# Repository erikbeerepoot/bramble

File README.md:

# Bramble

LoRa sensor and actuator network for farm monitoring, built on RP2040.

Hub-and-spoke architecture: a central hub manages the network while nodes collect sensor data (temperature, humidity) and control actuators (irrigation valves). LoRa provides long-range wireless with reliable delivery guarantees.

## Hardware

- Adafruit Feather RP2040 LoRa (SX1276, 915 MHz)
- MT25QL01GBBB 128MB external flash for sensor data storage
- STM32L010 PMU for power management and sleep

## Building

Requires the Pico SDK. CMake is bundled at `~/.pico-sdk/cmake/v3.31.5/bin/cmake`.

```bash
# Build a specific variant
cmake -B build -DHARDWARE_VARIANT=SENSOR
cmake --build build -j8

# Variants: SENSOR, IRRIGATION, CONTROLLER, HUB, GENERIC, ALL
```

Each variant produces a named executable (e.g. `bramble_sensor.uf2`).

```bash
# Run tests
cmake -B build -DBUILD_TESTS=ON
cmake --build build -j8
```

### Flashing

Hold BOOTSEL and connect via USB, then copy the `.uf2` file. Or use OpenOCD with a debug probe:

```bash
~/.pico-sdk/openocd/0.12.0+dev/openocd \
  -s ~/.pico-sdk/openocd/0.12.0+dev/scripts \
  -f interface/cmsis-dap.cfg -f target/rp2040.cfg \
  -c "adapter speed 5000" \
  -c "program build/bramble_sensor.elf verify reset exit"
```

## Architecture

```
[Sensor Nodes] --LoRa--> [Hub/Pico] --Serial--> [Raspberry Pi] --REST--> [Dashboard]
                               |                       |
                          128MB Flash              DuckDB
                        (local buffer)          (long-term storage)
```

### Firmware (`src/`)

- `modes/` - Application modes per hardware variant (sensor, irrigation, hub, etc.)
- `lora/` - SX1276 driver, message protocol, reliable delivery, routing
- `hal/` - Hardware abstraction (flash, NeoPixel, valves, SPI)
- `storage/` - 128MB circular flash buffer for sensor records
- `config/` - Persistent node/hub configuration

### API (`api/`)

Flask REST API on the Raspberry Pi. Receives sensor data from the hub over serial, stores in DuckDB.

```bash
cd api && uv sync && uv run app.py
```

### Dashboard (`dashboard/`)

React SPA for viewing sensor data, managing nodes, and organizing zones.

```bash
cd dashboard && npm install && npm run dev
```

## Setup

After cloning:

```bash
./setup.sh  # configures git hooks
```

See `CLAUDE.md` for development guidelines and `PLAN.md` for the roadmap.

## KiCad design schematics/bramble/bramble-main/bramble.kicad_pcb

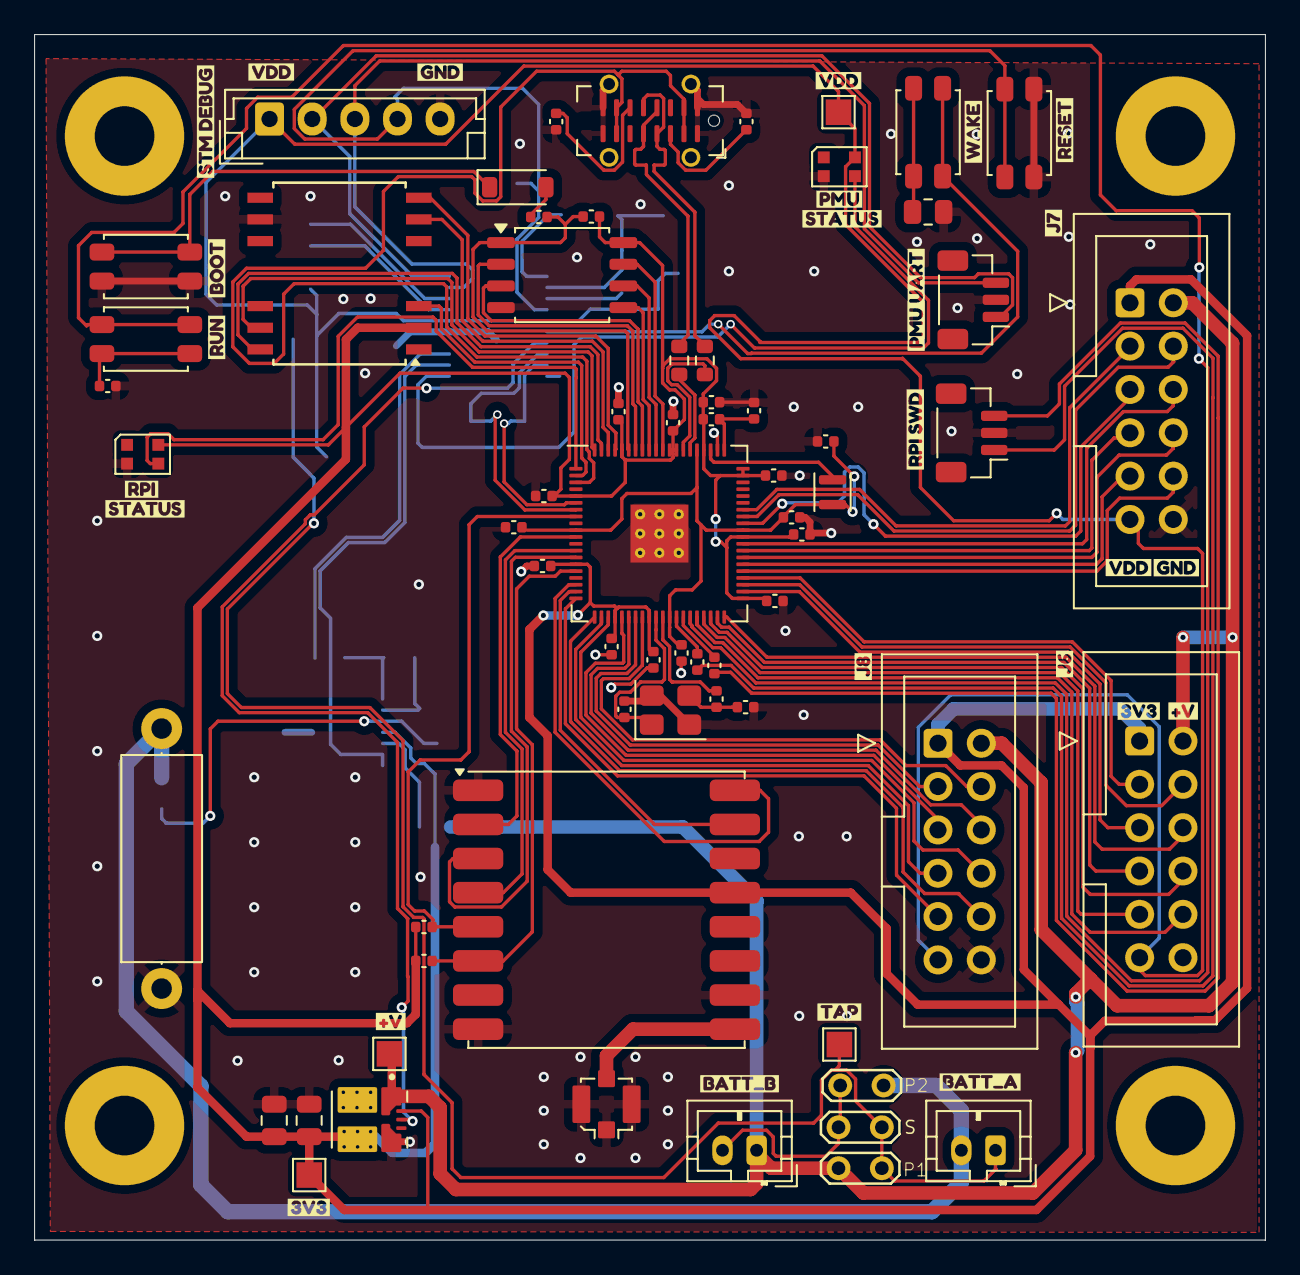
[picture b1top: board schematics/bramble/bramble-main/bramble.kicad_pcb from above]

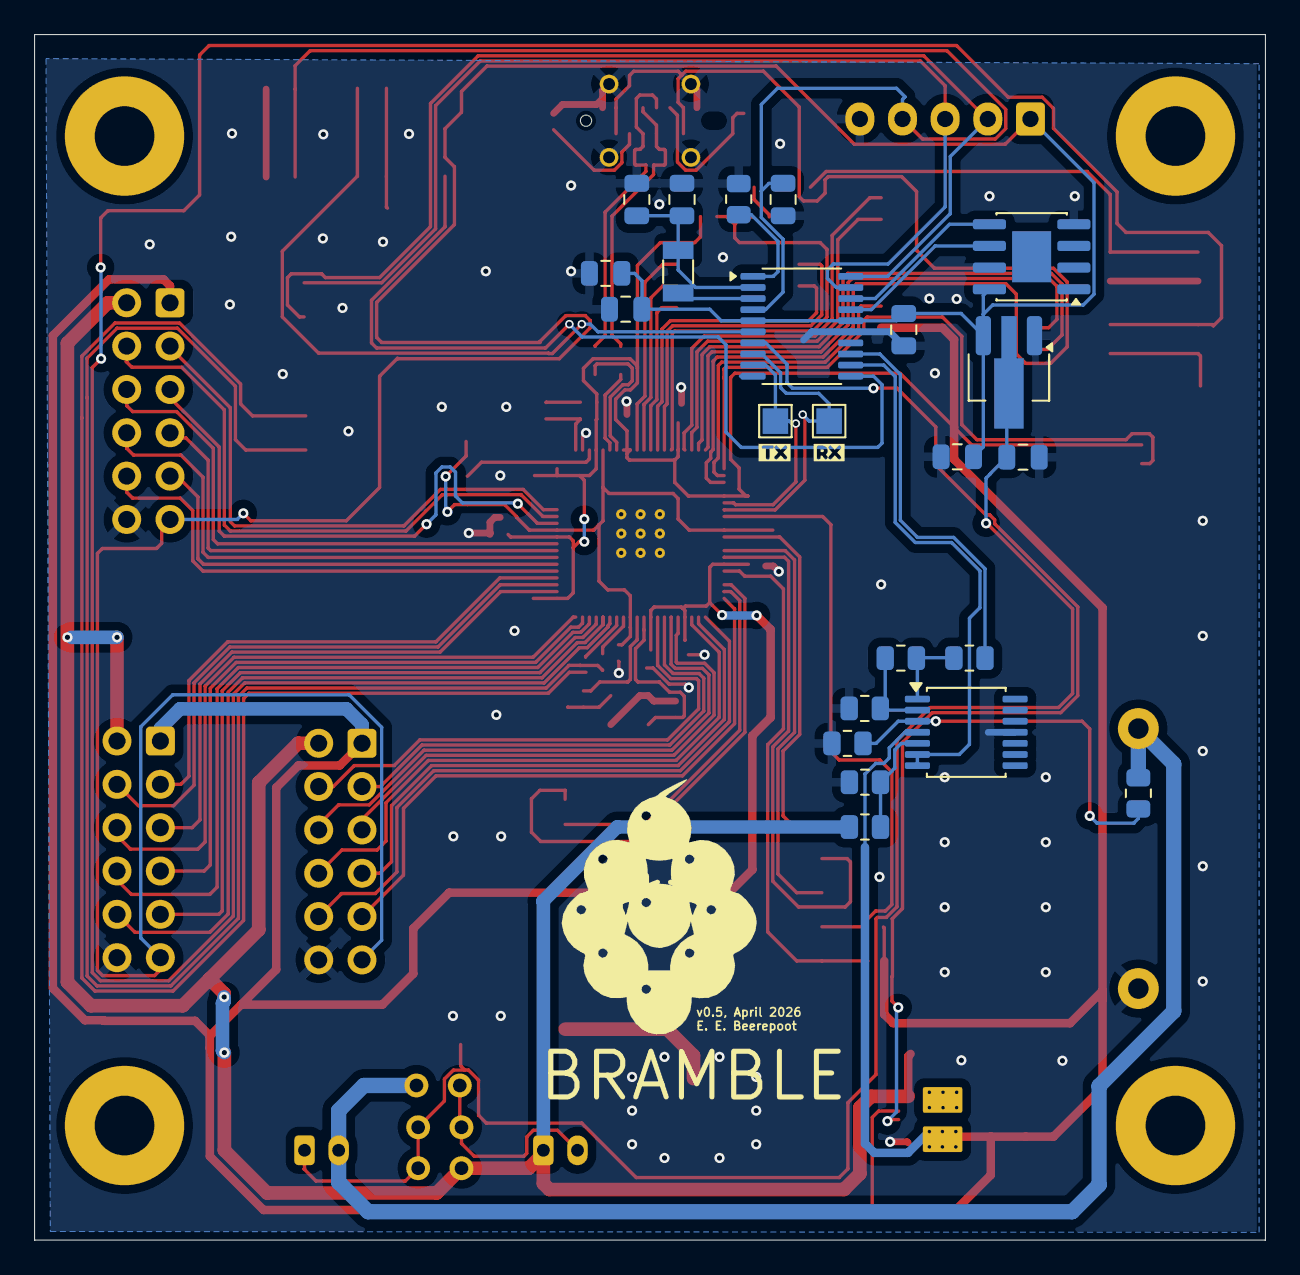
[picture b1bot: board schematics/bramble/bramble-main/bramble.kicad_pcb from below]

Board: 2 copper layers, 72.1 x 70.7 mm, 120 parts (25 on the bottom side), 91 nets.

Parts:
C1: 10uF; C_0805_2012Metric
C2: 22uF; C_0805_2012Metric
C3: 4.7uF; C_0805_2012Metric
C4, C5, C8: 100nF; C_0805_2012Metric
C6, C7: 1uF; C_0805_2012Metric
C9, C10: 10pF; C_0805_2012Metric
C11, C12, C14, C15: 4.7uF; C_0402_1005Metric
C13, C16, C17, C18, C19, C20, C21, C22, C23, C24, C27: 100nF; C_0402_1005Metric
C25, C26: 15p; C_0402_1005Metric
D1: 1N4148W; D_SOD-123
H1, H2, H3, H4: MountingHole; MountingHole_3.5mm_Pad
J1: Conn_01x05_Pin; JST_EH_B5B-EH-A_1x05_P2.50mm_Vertical
J2: UART; JST_SH_BM03B-SRSS-TB_1x03-1MP_P1.00mm_Vertical
J3: RPI SWD; JST_SH_BM03B-SRSS-TB_1x03-1MP_P1.00mm_Vertical
J4: U.FL; U.FL_Molex_MCRF_73412-0110_Vertical
J5: USB_C_Receptacle_USB2.0_16P; USB_C_Receptacle_G-Switch_GT-USB-7051x
J6: GPIO1; IDC-Header_2x06_P2.54mm_Vertical
J7: GPIO2; IDC-Header_2x06_P2.54mm_Vertical
J8: GPIO3; IDC-Header_2x06_P2.54mm_Vertical
JP1: Series; TestPoint_2Pads_Pitch2.54mm_Drill0.8mm
JP2: Parallel 1; TestPoint_2Pads_Pitch2.54mm_Drill0.8mm
JP3: Parallel 2; TestPoint_2Pads_Pitch2.54mm_Drill0.8mm
L1: 3.3uH; L_Murata_DFE201610P
MAIN_SUPPLY1: B2B-PH-K-S; JST_PH_B2B-PH-K_1x02_P2.00mm_Vertical
PMU_STATUS1: WS2812B-2020; LED_WS2812B-2020_PLCC4_2.0x2.0mm
PMU_SUPPLY1: B2B-PH-K-S; JST_PH_B2B-PH-K_1x02_P2.00mm_Vertical
R1, R3, R6: 1k; R_0805_2012Metric
R2: 100; R_0805_2012Metric
R4: 0.1; R_Axial_DIN0414_L11.9mm_D4.5mm_P15.24mm_Horizontal
R5, R9, R10: 10k; R_0805_2012Metric
R7: 20k; R_0805_2012Metric
R8: 8.2k; R_0805_2012Metric
R11, R12, R23: 10k; C_0402_1005Metric
R13: 33; C_0402_1005Metric
R14, R15: 100; C_0402_1005Metric
R16, R17, R21, R22: 1K; C_0402_1005Metric
R18, R19: 27; R_0603_1608Metric
R20: 5.1K; C_0402_1005Metric
RPI_STATUS1: WS2812B-2020; LED_WS2812B-2020_PLCC4_2.0x2.0mm
STM_RESET1: STM_RESET; SW_SPST_EVQP2_MiddlePushTravel_H2.5mm
STM_WAKE1: STM_WAKE; SW_SPST_EVQP2_MiddlePushTravel_H2.5mm
SW1: BOOT; SW_SPST_EVQP2_MiddlePushTravel_H2.5mm
SW2: RESET; SW_SPST_EVQP2_MiddlePushTravel_H2.5mm
TP1: 3V3 TEST; TestPoint_Pad_1.5x1.5mm
TP2: RX_TEST; TestPoint_Pad_1.5x1.5mm
TP3: TX_TEST; TestPoint_Pad_1.5x1.5mm
TP4: MAINS TEST; TestPoint_Pad_1.5x1.5mm
TP5: TAP TEST; TestPoint_Pad_1.5x1.5mm
TP6: PMU SUPPLY TEST; TestPoint_Pad_1.5x1.5mm
U1: Opamp_Quad; TSSOP-14_4.4x5mm_P0.65mm
U2: STM32L031F6P6TR; TSSOP-20_4.4x6.5mm_P0.65mm
U3: MCP1700x-120xxMB; SOT-89-3_Handsoldering
U4: FM24CL16B-GTR; SOIC-8-1EP_3.9x4.9mm_P1.27mm_EP2.29x3mm
U5: NiceRF Lora1262; HOPERF_RFM9XW_SMD
U6: RP2350_80QFN; RP2350-QFN-80-1EP_10x10_P0.4mm_EP3.4x3.4mm_ThermalVias
U7: W25Q16JVSS; SOIC-8_5.3x5.3mm_P1.27mm
U8: MT25QL01GBBB8ESF-0SIT; SOIC-16W-12_7.5x10.3mm_P1.27mm
VR1: TPSM861253RDXR; VREG_TPSM861253RDXR
Y1: Crystal; Crystal_SMD_3215-2Pin_3.2x1.5mm
Y2: ABM8-272-T3; Crystal_SMD_3225-4Pin_3.2x2.5mm
kibuzzard-69F1F93E: G***; kibuzzard-69F1F93E
kibuzzard-69F1F948: G***; kibuzzard-69F1F948
kibuzzard-69F1FA9E: G***; kibuzzard-69F1FA9E
kibuzzard-69F1FABA: G***; kibuzzard-69F1FABA
kibuzzard-69F1FACD, kibuzzard-69F1FACD#2: G***; kibuzzard-69F1FACD
kibuzzard-69F1FAE9: G***; kibuzzard-69F1FAE9
kibuzzard-69F1FB2A, kibuzzard-69F1FB2A#2: G***; kibuzzard-69F1FB2A
kibuzzard-69F1FB3C: G***; kibuzzard-69F1FB3C
kibuzzard-69F1FB5C: G***; kibuzzard-69F1FB5C
kibuzzard-69F1FB6D: G***; kibuzzard-69F1FB6D
kibuzzard-69F1FB08: G***; kibuzzard-69F1FB08
kibuzzard-69F1FB43: G***; kibuzzard-69F1FB43
kibuzzard-69F1FBEC: G***; kibuzzard-69F1FBEC
kibuzzard-69F1FC5E: G***; kibuzzard-69F1FC5E
kibuzzard-69F15CED: G***; kibuzzard-69F15CED
kibuzzard-69F15D5F, kibuzzard-69F15D5F#2: G***; kibuzzard-69F15D5F
kibuzzard-69F15D28: G***; kibuzzard-69F15D28
kibuzzard-69F15D48, kibuzzard-69F15D48#2: G***; kibuzzard-69F15D48
kibuzzard-69F15DA2: G***; kibuzzard-69F15DA2
kibuzzard-69F20A0D: G***; kibuzzard-69F20A0D
kibuzzard-69F20A1A: G***; kibuzzard-69F20A1A
kibuzzard-69F204CF: G***; kibuzzard-69F204CF
kibuzzard-69F204DC: G***; kibuzzard-69F204DC
kibuzzard-69F209F9: G***; kibuzzard-69F209F9

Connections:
+1V1: C12.1, C13.1, C15.1, C16.1, L1.1, U6.10 (DVDD), U6.32 (DVDD), U6.51 (DVDD), U6.65 (VREG_FB)
+3V3: C1.1, C2.1, C11.1, C17.1, C18.1, C19.1, C20.1, C21.1, C22.1, C23.1, C24.1, C27.1, J6.1, J7.1, J8.1, R11.2, R12.2, R13.1, R23.1, RPI_STATUS1.4 (VDD), TP1.1, U1.4 (V+), U5.13 (3.3V), U6.5 (IOVDD), U6.15 (IOVDD), U6.24 (IOVDD), U6.29 (IOVDD), U6.41 (IOVDD), U6.50 (IOVDD), U6.59 (ADC_AVDD), U6.60 (IOVDD), U6.64 (VREG_VIN), U6.68 (USB_OTP_VDD), U6.69 (QSPI_IOVDD), U6.76 (IOVDD), U7.8 (VCC), U8.2 (VCC), VR1.3 (VOUT), VR1.7 (VOS)
+9V: J6.2, J7.2, J8.2, JP2.1 (A), MAIN_SUPPLY1.1, R7.2, TP4.1, VR1.1 (VIN)
/pmu/3V3_POWER_ON: U2.7 (PA1), VR1.6 (EN)
/pmu/MEAS_CURRENT: R6.1, U2.13 (PA7)
/pmu/MEAS_V: U1.6 (-), U1.7, U2.12 (PA6)
/pmu/NRST: C8.2, J1.4, STM_RESET1.1, U2.4 (NRST)
/pmu/SCL: U2.17 (PA9), U4.6 (SCL)
/pmu/SDA: U2.18 (PA10), U4.5 (SDA)
/rp2350B (page 4)/D+: J5.A6 (D+), J5.B6 (D+), R18.2
/rp2350B (page 4)/D-: J5.A7 (D-), J5.B7 (D-), R19.2
/rp2350B (page 4)/GPIO20: J8.9, U6.20 (GPIO20)
/rp2350B (page 4)/GPIO21: J8.10, U6.21 (GPIO21)
/rp2350B (page 4)/GPIO22: J8.7, U6.22 (GPIO22)
/rp2350B (page 4)/GPIO23: J8.8, U6.23 (GPIO23)
/rp2350B (page 4)/GPIO24: J8.5, U6.25 (GPIO24)
/rp2350B (page 4)/GPIO25: J8.6, U6.26 (GPIO25)
/rp2350B (page 4)/GPIO26: J8.3, U6.27 (GPIO26)
/rp2350B (page 4)/GPIO27: J8.4, U6.28 (GPIO27)
/rp2350B (page 4)/GPIO28: J7.10, U6.45 (GPIO36)
/rp2350B (page 4)/GPIO29: J7.9, U6.46 (GPIO37)
/rp2350B (page 4)/GPIO30: J7.8, U6.47 (GPIO38)
/rp2350B (page 4)/GPIO31: J7.7, U6.48 (GPIO39)
/rp2350B (page 4)/GPIO40_ADC0: J7.6, U6.49 (GPIO40_ADC0)
/rp2350B (page 4)/GPIO41_ADC1: J7.5, U6.52 (GPIO41_ADC1)
/rp2350B (page 4)/GPIO42_ADC2: J7.4, U6.53 (GPIO42_ADC2)
/rp2350B (page 4)/GPIO43_ADC3: J7.3, U6.54 (GPIO43_ADC3)
/rp2350B (page 4)/MISO: U5.2 (MISO), U6.11 (GPIO12)
/rp2350B (page 4)/MOSI: U5.3 (MOSI), U6.14 (GPIO15)
/rp2350B (page 4)/MOTOR_HI_1: J6.10, U6.36 (GPIO28)
/rp2350B (page 4)/MOTOR_HI_2: J6.8, U6.38 (GPIO30)
/rp2350B (page 4)/MOTOR_LO_1: J6.6, U6.40 (GPIO32)
/rp2350B (page 4)/MOTOR_LO_2: J6.4, U6.43 (GPIO34)
/rp2350B (page 4)/MT25_CS: U6.78 (GPIO1), U8.7 (S#)
/rp2350B (page 4)/MT25_MISO: U6.77 (GPIO0), U8.8 (DQ1)
/rp2350B (page 4)/MT25_MOSI: U6.80 (GPIO3), U8.15 (DQ0)
/rp2350B (page 4)/MT25_RESET: U6.2 (GPIO5), U8.3 (RESET#)
/rp2350B (page 4)/MT25_SCK: U6.79 (GPIO2), U8.16 (C)
/rp2350B (page 4)/QSPI_D0: U6.72 (QSPI_SD0), U7.5 (DI/IO_{0})
/rp2350B (page 4)/QSPI_D1: U6.74 (QSPI_SD1), U7.2 (DO/IO_{1})
/rp2350B (page 4)/QSPI_D2: U6.73 (QSPI_SD2), U7.3 (~WP/IO_{2})
/rp2350B (page 4)/QSPI_D3: U6.70 (QSPI_SD3), U7.7 (~HOLD/~RESET/IO_{3})
/rp2350B (page 4)/QSPI_SCK: U6.71 (QSPI_SCLK), U7.6 (CLK)
/rp2350B (page 4)/QSPI_SS: R16.1, R23.2, U6.75 (QSPI_SS), U7.1 (~CS)
/rp2350B (page 4)/RFM_BUSY: U5.16 (BUSY), U6.18 (GPIO18)
/rp2350B (page 4)/RFM_CS: R12.1, U5.5 (NSS), U6.8 (GPIO10)
/rp2350B (page 4)/RFM_IO1: U5.15 (DIO1), U6.19 (GPIO19)
/rp2350B (page 4)/RFM_RST: R11.1, U5.6 (RESET), U6.16 (GPIO16)
/rp2350B (page 4)/RGB_LED: RPI_STATUS1.3 (DIN), U6.1 (GPIO4)
/rp2350B (page 4)/RUN: SW2.1, U6.35 (RUN)
/rp2350B (page 4)/RX: TP3.1, U2.8 (PA2), U6.7 (GPIO9)
/rp2350B (page 4)/SCK: U5.4 (SCK), U6.13 (GPIO14)
/rp2350B (page 4)/TX: TP2.1, U2.9 (PA3), U6.6 (GPIO8)
/rp2350B (page 4)/USBBOOT: D1.1 (K), SW1.1
/rp2350B (page 4)/VALVE_1: J6.9, U6.37 (GPIO29)
/rp2350B (page 4)/VALVE_2: J6.7, U6.39 (GPIO31)
/rp2350B (page 4)/VALVE_3: J6.3, U6.44 (GPIO35)
/rp2350B (page 4)/VALVE_4: J6.5, U6.42 (GPIO33)
/rp2350B (page 4)/VREG_AVDD: C14.1, R13.2, U6.61 (VREG_AVDD)
/rp2350B (page 4)/VREG_LX: L1.2, U6.63 (VREG_LX)
/rp2350B (page 4)/XIN: C25.1, U6.30 (XIN), Y2.1
/rp2350B (page 4)/XOUT: R22.2, U6.31 (XOUT)
GND: C1.2, C2.2, C3.2, C4.2, C5.2, C6.1, C7.1, C8.1, C9.2, C10.2, C11.2, C12.2, C13.2, C14.2, C15.2, C16.2, C17.2, C18.2, C19.2, C20.2, C21.2, C22.2, C23.2, C24.2, C25.2, C26.2, C27.2, J1.5, J2.2, J3.2, J4.2 (Ext), J5.A1 (GND), J5.A12 (GND), J5.B1 (GND), J5.B12 (GND), J5.S1 (SHIELD), J6.12, J7.12, J8.12, PMU_STATUS1.2 (VSS), R2.2, R3.1, R4.1, R8.1, R9.1, R10.2, R17.1, R20.2, R21.2, RPI_STATUS1.2 (VSS), STM_RESET1.2, SW1.2, U1.11 (V-), U2.15 (VSS), U3.1 (GND), U4.4 (GND), U4.7 (WP), U5.1 (GND), U5.8 (GND), U5.10 (GND), U6.62 (VREG_PGND), U6.81 (GND), U7.4 (GND), U8.10 (VSS), VR1.4 (PGND), Y2.2, Y2.4
GNDPWR: JP3.2 (B), PMU_SUPPLY1.2, R1.2, R4.2
unnamed: C26.1, R22.1, Y2.3
unnamed: D1.2 (A), R16.2
unnamed: J1.2, J2.1, U2.20 (PA14)
unnamed: J1.3, J2.3, U2.19 (PA13)
unnamed: J3.1, R14.1
unnamed: J3.3, R15.1
unnamed: J4.1 (In), U5.9 (ANT)
unnamed: J5.A5 (CC1), R21.1
unnamed: J5.B5 (CC2), R20.1
unnamed: JP1.1 (A), JP3.1 (A), MAIN_SUPPLY1.2
unnamed: C6.2, JP1.2 (B), JP2.2 (B), PMU_SUPPLY1.1, TP5.1, U3.2 (VI)
unnamed: PMU_STATUS1.3 (DIN), U2.11 (PA5)
unnamed: R5.2, R6.2, U1.1
unnamed: R9.2, STM_WAKE1.1
unnamed: R17.2, SW2.2
unnamed: R1.1, R2.1, U1.3 (+)
unnamed: R3.2, R5.1, U1.2 (-)
unnamed: R7.1, R8.2, U1.5 (+)
unnamed: STM_WAKE1.2, U2.6 (PA0-CK_IN)
unnamed: R10.1, U2.1 (PB9-BOOT0)
unnamed: C9.1, C10.1, U2.2 (PC14-OSC32_IN), U2.3 (PC15-OSC32_OUT), Y1.1, Y1.2
unnamed: R14.2, U6.33 (SWCLK)
unnamed: R15.2, U6.34 (SWD)
unnamed: R19.1, U6.66 (USB_DM)
unnamed: R18.1, U6.67 (USB_DP)
VBUS: J5.A4 (VBUS), J5.A9 (VBUS), J5.B4 (VBUS), J5.B9 (VBUS), U6.3 (GPIO6)
VDD: C3.1, C4.1, C5.1, C7.2, J1.1, J6.11, J7.11, J8.11, PMU_STATUS1.4 (VDD), TP6.1, U2.5 (VDDA), U2.16 (VDD), U3.3 (VO), U4.8 (VCC)

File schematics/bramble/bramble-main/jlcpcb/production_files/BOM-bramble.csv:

Comment,Designator,Footprint,LCSC,Quantity
100,R2,R_0805_2012Metric,C17408,1
100,"R14,R15",C_0402_1005Metric,C25076,2
100nF,"C13,C16,C17,C18,C19,C20,C21,C22,C23,C24",C_0402_1005Metric,C1525,10
100nF,"C4,C5,C8",C_0805_2012Metric,C28233,3
100nF,C27,C_0402_1005Metric,C49678,1
10k,"R10,R5,R9",R_0805_2012Metric,C17414,3
10k,"R11,R12",C_0402_1005Metric,C25744,2
10pF,"C10,C9",C_0805_2012Metric,C1839,2
10uF,C1,C_0805_2012Metric,C15850,1
15p,"C25,C26",C_0402_1005Metric,C1548,2
1K,"R16,R17,R21,R22",C_0402_1005Metric,C11702,4
1N4148W,D1,D_SOD-123,C81598,1
1k,"R1,R3,R6",R_0805_2012Metric,C17513,3
1uF,"C6,C7",C_0805_2012Metric,C28323,2
20k,R7,R_0805_2012Metric,C4328,1
22uF,C2,C_0805_2012Metric,C45783,1
27,"R18,R19",R_0603_1608Metric,C25190,2
3.3uH,L1,L_Murata_DFE201610P,C42411119,1
33,R13,C_0402_1005Metric,C25105,1
4.7uF,C3,C_0805_2012Metric,C1779,1
4.7uF,"C11,C12,C14,C15",C_0402_1005Metric,C23733,4
5.1K,R20,C_0402_1005Metric,C25905,1
8.2k,R8,R_0805_2012Metric,C17828,1
ABM8-272-T3,Y2,Crystal_SMD_3225-4Pin_3.2x2.5mm,C20625731,1
BOOT,SW1,SW_SPST_EVQP2_MiddlePushTravel_H2.5mm,C528967,1
Conn_01x05_Pin,J1,JST_EH_B5B-EH-A_1x05_P2.50mm_Vertical,C160256,1
Crystal,Y1,Crystal_SMD_3215-2Pin_3.2x1.5mm,C182057,1
FM24CL16B-GTR,U4,SOIC-8-1EP_3.9x4.9mm_P1.27mm_EP2.29x3mm,C31082,1
GPIO1,J6,IDC-Header_2x06_P2.54mm_Vertical,C9136,1
GPIO2,J7,IDC-Header_2x06_P2.54mm_Vertical,C9136,1
GPIO3,J8,IDC-Header_2x06_P2.54mm_Vertical,C9136,1
MCP1700x-120xxMB,U3,SOT-89-3_Handsoldering,C57883,1
MT25QL01GBBB8ESF-0SIT,U8,SOIC-16W-12_7.5x10.3mm_P1.27mm,C427722,1
NiceRF Lora1262,U5,HOPERF_RFM9XW_SMD,C5356643,1
Opamp_Quad,U1,TSSOP-14_4.4x5mm_P0.65mm,C2902316,1
RESET,SW2,SW_SPST_EVQP2_MiddlePushTravel_H2.5mm,C528967,1
RP2350_80QFN,U6,RP2350-QFN-80-1EP_10x10_P0.4mm_EP3.4x3.4mm_ThermalVias,C42415655,1
RPI SWD,J3,JST_SH_BM03B-SRSS-TB_1x03-1MP_P1.00mm_Vertical,C160389,1
STM32L031F6P6TR,U2,TSSOP-20_4.4x6.5mm_P0.65mm,C2054042,1
TPSM861253RDXR,VR1,VREG_TPSM861253RDXR,C31183817,1
UART,J2,JST_SH_BM03B-SRSS-TB_1x03-1MP_P1.00mm_Vertical,C160389,1
USB_C_Receptacle_USB2.0_16P,J5,USB_C_Receptacle_G-Switch_GT-USB-7051x,C2843970,1
W25Q16JVSS,U7,SOIC-8_5.3x5.3mm_P1.27mm,C131025,1
Series,JP1,TestPoint_2Pads_Pitch2.54mm_Drill0.8mm,,1
Parallel 1,JP2,TestPoint_2Pads_Pitch2.54mm_Drill0.8mm,,1
Parallel 2,JP3,TestPoint_2Pads_Pitch2.54mm_Drill0.8mm,,1
TAP TEST,TP5,TestPoint_Pad_1.5x1.5mm,,1
U.FL,J4,U.FL_Molex_MCRF_73412-0110_Vertical,,1
0.1,R4,R_Axial_DIN0414_L11.9mm_D4.5mm_P15.24mm_Horizontal,,1
PMU SUPPLY TEST,TP6,TestPoint_Pad_1.5x1.5mm,,1
10k,R23,C_0402_1005Metric,,1
3V3 TEST,TP1,TestPoint_Pad_1.5x1.5mm,,1
RX_TEST,TP2,TestPoint_Pad_1.5x1.5mm,,1
TX_TEST,TP3,TestPoint_Pad_1.5x1.5mm,,1
MAINS TEST,TP4,TestPoint_Pad_1.5x1.5mm,,1

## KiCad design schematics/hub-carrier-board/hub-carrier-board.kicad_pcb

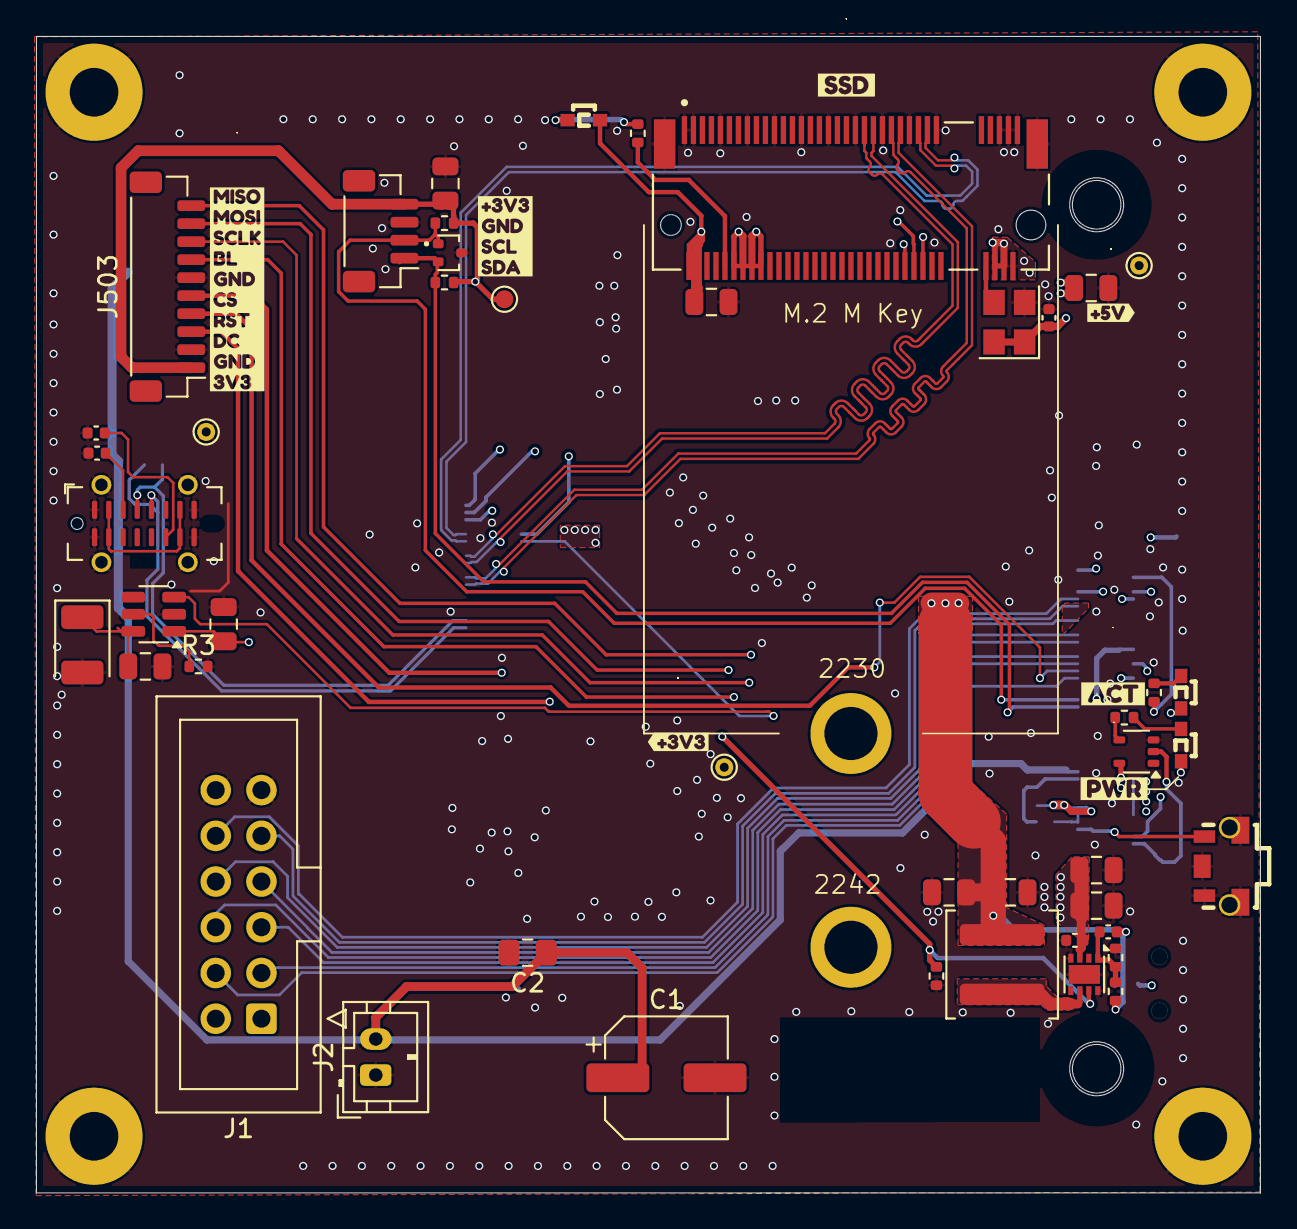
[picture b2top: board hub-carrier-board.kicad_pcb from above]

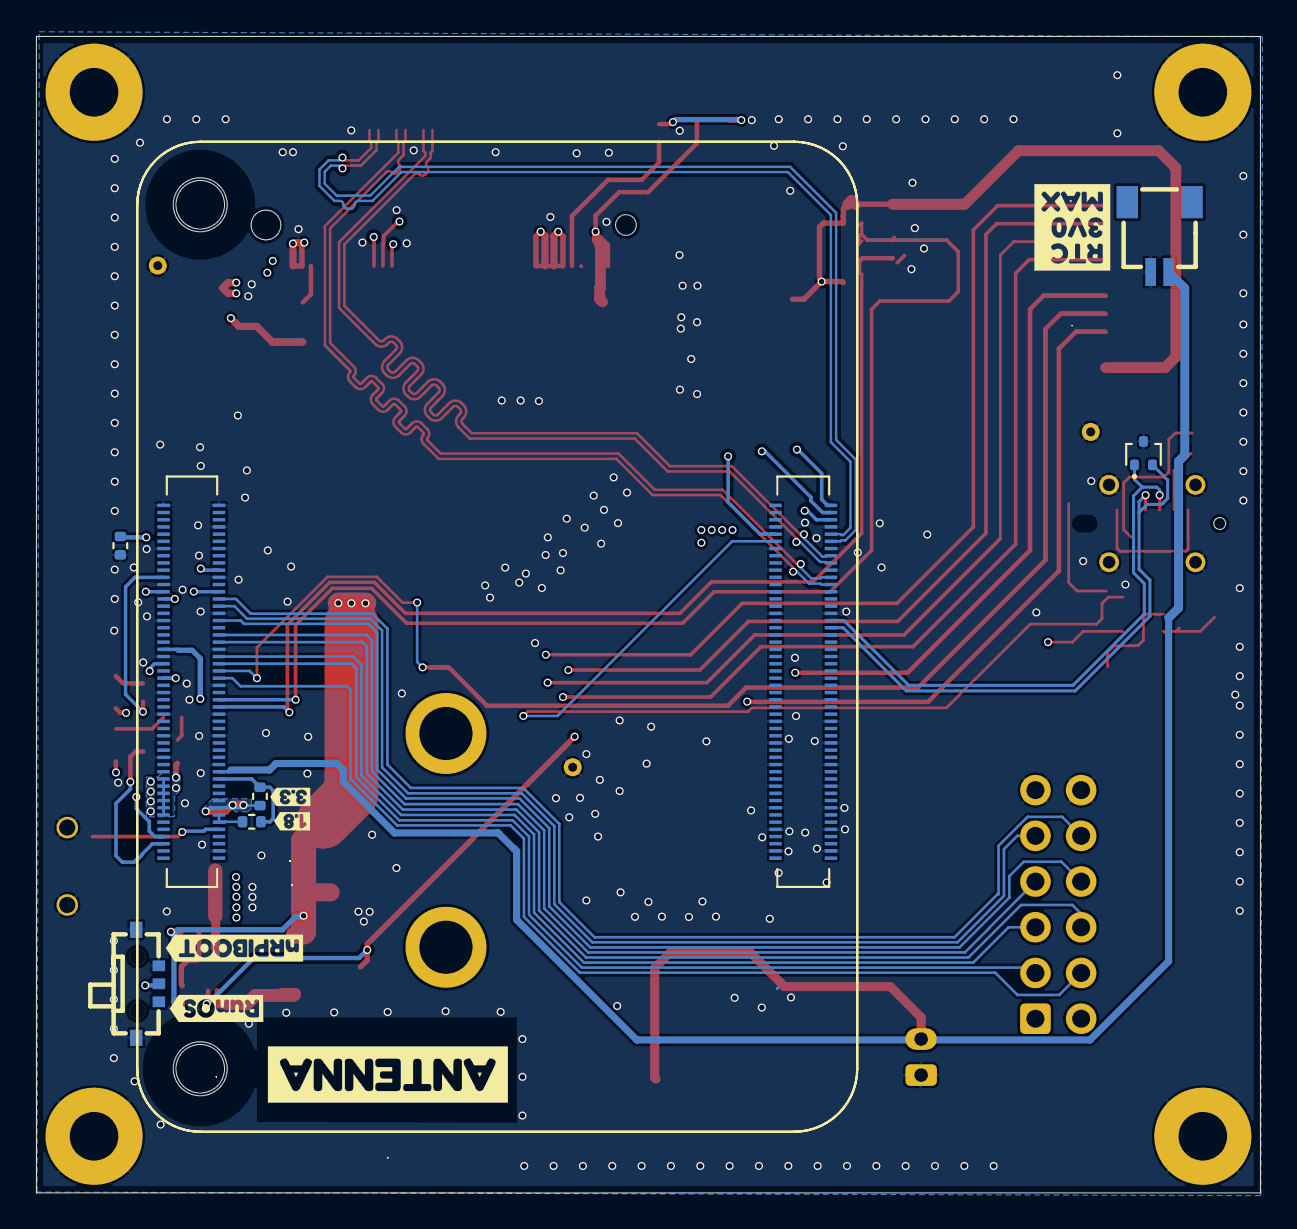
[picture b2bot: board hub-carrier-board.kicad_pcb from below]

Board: 4 copper layers, 68.0 x 64.2 mm, 73 parts (14 on the bottom side), 56 nets.

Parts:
C1: 470; CP_Elec_6.3x7.7
C2: 100nF; C_0805_2012Metric_Pad1.18x1.45mm_HandSolder
C601: 4u7; C_0805_2012Metric
C701, C703, C704, C705, C708, C709, C710, C711: 10u; C_0805_2012Metric
C702: 100uF; CP_EIA-3528-21_Kemet-B
C706, C712: 100n; C_0402_1005Metric
C707: 4.7nF; C_0402_1005Metric
CN1: SM02B-SRSS-TB (LF)(SN); CONN-SMD_2P-P1.00_SM02B-SRSS-TB-LF-SN
D502, D701: RCLAMP0502BA; SOT-416
D605, D606, D702: GREEN; LED-SMD_L1.7-W0.6-RD
H102, H103, H104, H105: MountingHole_Pad; MountingHole_2.7mm_Pad
J1: GPIO1; IDC-Header_2x06_P2.54mm_Vertical
J2: PWR; JST_PH_B2B-PH-K_1x02_P2.00mm_Vertical
J5: USB_C_Receptacle_USB2.0_16P; USB_C_Receptacle_G-Switch_GT-USB-7051x
J101: ComputeModule5-CM5; Raspberry-Pi-5-Compute-Module_GPIO
J102: ComputeModule5-CM5; Raspberry-Pi-5-Compute-Module_HSS
J502: I2C; JST_SH_BM04B-SRSS-TB_1x04-1MP_P1.00mm_Vertical
J503: SPI; JST_SH_BM10B-SRSS-TB_1x10-1MP_P1.00mm_Vertical
J701: Bus_M.2_Socket_M; M.2 M Key socket_2230_2242
L701: 2.2uH; L_Coilcraft_XAL5030-XXX
M701, M702: M.2 Solder Nut; MountingHole_3mm_Pad
R3: 15k; R_0402_1005Metric
R20, R21: 5.1K; C_0402_1005Metric
R102, R103: 0R; R_0402_1005Metric
R104, R705: 10k; R_0402_1005Metric
R501, R502, R605, R606, R706, R707: 2k2; R_0402_1005Metric
R704: 100k; R_0402_1005Metric
SW101: MK-11C04-G013; SW-SMD_MK-11C04-G013
SW501: TS-1010A-B; SW-SMD_TS-1010A-B
TP103: +3V3_PI; TestPoint_Pad_D1.0mm
TP104, TP105, TP106: GND; TestPoint_THTPad_D1.0mm_Drill0.5mm
U602: SN74LVC1G14DBVR; SOT-353_SC-70-5
U701: AP22653W6; SOT-23-6
U702: AP3441SHE-7B; DFN-8-1EP_2x2mm_P0.5mm_EP1.05x1.75mm
U703: ASEK-32.768KHZ-L-R-T; Crystal_SMD_3225-4Pin_3.2x2.5mm
kibuzzard-67CC6BD3: G***; kibuzzard-67CC6BD3
kibuzzard-67CC6D9E: G***; kibuzzard-67CC6D9E
kibuzzard-67CC6D94: G***; kibuzzard-67CC6D94
kibuzzard-67CC7445: G***; kibuzzard-67CC7445
kibuzzard-67EBAC4C: G***; kibuzzard-67EBAC4C
kibuzzard-67EBB9C1: G***; kibuzzard-67EBB9C1
kibuzzard-67EBF0A0: G***; kibuzzard-67EBF0A0
kibuzzard-69AD8816: G***; kibuzzard-69AD8816
kibuzzard-6773B9CA: G***; kibuzzard-6773B9CA
kibuzzard-6773B9F7: G***; kibuzzard-6773B9F7
kibuzzard-6773BA89: G***; kibuzzard-6773BA89
kibuzzard-6773C376: G***; kibuzzard-6773C376
kibuzzard-67795592: G***; kibuzzard-67795592

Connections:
+1V8: J101.88 (+1.8v_(Output)), J101.90 (+1.8v_(Output)), R103.1
+3V3_PI: C601.1, J101.84 (+3.3v_(Output)), J101.86 (+3.3v_(Output)), J502.4, J503.1, R102.1, R501.1, R502.1, TP103.1
+5V: C1.1, C2.1, C701.1, C704.1, C705.1, C706.1, D605.2 (A), D606.2 (A), J2.2, U602.5 (VCC), U701.1 (IN), U702.3 (VIN)
+BATT: CN1.1, J101.76 (VBAT)
/CM5/+5V: J101.77 (+5v_(Input)), J101.79 (+5v_(Input)), J101.81 (+5v_(Input)), J101.83 (+5v_(Input)), J101.85 (+5v_(Input)), J101.87 (+5v_(Input))
/CM5/BL_GPIO24: J101.45 (GPIO24), J503.7
/CM5/CS_GPIO18: J101.49 (GPIO18), J503.5
/CM5/DC_GPI25: J101.41 (GPIO25), J503.3
/CM5/EEPROM_nWP: J101.20 (EEPROM_nWP), R104.2
/CM5/GPIO_VREF: J101.78 (GPIO_VREF(1.8v/3.3v_Input)), R102.2, R103.2
/CM5/MISO_GPIO19: J101.26 (GPIO19), J503.10
/CM5/MOSI_GPIO20: J101.27 (GPIO20), J503.9
/CM5/PCIE_PI.CLK_N: J102.112 (PCIe_CLK_N), J701.53 (REFCLKn)
/CM5/PCIE_PI.CLK_P: J102.110 (PCIe_CLK_P), J701.55 (REFCLKp)
/CM5/PCIE_PI.PWR_EN: J102.106 (PCIE_PWR_EN), R704.1, U702.7 (EN)
/CM5/PCIE_PI.RX_N: J102.118 (PCIe_RX_N), J701.43 (PETp0)
/CM5/PCIE_PI.RX_P: J102.116 (PCIe_RX_P), J701.41 (PETn0)
/CM5/PCIE_PI.TX_N: J102.124 (PCIe_TX_N), J701.49 (PERp0)
/CM5/PCIE_PI.TX_P: J102.122 (PCIe_TX_P), J701.47 (PERn0)
/CM5/PCIE_PI.nCLKREQ: J102.102 (PCIe_nCLKREQ), J701.52 (~CLKREQ)
/CM5/PCIE_PI.nRST: J102.109 (PCIe_nRST), J701.50 (~PERST)
/CM5/PCIE_PI.nWAKE: J102.104 (PCIE_nWAKE), J701.54 (~PEWAKE)
/CM5/PI_nLED_PWR: J101.95 (LED_nPWR), U602.2
/CM5/PWR_BUT: J101.92 (PWR_BUT), SW501.1
/CM5/RST_GPIO27: J101.48 (GPIO27), J503.4
/CM5/SCL1_IO3: D502.1 (K1), J101.56 (GPIO3), J502.2, R502.2
/CM5/SCLK_GPIO21: J101.25 (GPIO21), J503.8
/CM5/SDA1_IO2: D502.2 (K2), J101.58 (GPIO2), J502.1, R501.2
/CM5/VBUS_EN: J102.111 (VBUS_EN), U701.3 (EN)
/CM5/nLED_ACTIVITY: J101.21 (LED_nACT), R606.2
/CM5/nRPIBOOT: J101.93 (nRPIBOOT), SW101.C
/PCIe-M2/FB: C707.2, R705.2, R706.1, U702.1 (FB)
/PCIe-M2/M2_LX: L701.1, U702.6 (LX)
D+: D701.1 (K1), J5.A6 (D+), J102.134 (USB3-0-D_P)
D-: D701.2 (K2), J5.A7 (D-), J102.136 (USB3-0-D_N)
GND: C1.2, C2.2, C601.2, C701.2, C702.2, C703.2, C704.2, C705.2, C706.2, C708.2, C709.2, C710.2, C711.2, C712.2, CN1.2, D502.3 (A), D701.3 (A), H102.1, H103.1, H104.1, H105.1, J1.11, J1.12, J2.1, J5.A1 (GND), J5.A12 (GND), J5.B1 (GND), J5.B12 (GND), J5.S1 (SHIELD), J101.1 (GND), J101.2 (GND), J101.8 (GND), J101.13 (GND), J101.14 (GND), J101.22 (GND), J101.23 (GND), J101.32 (GND), J101.33 (GND), J101.42 (GND), J101.43 (GND), J101.52 (GND), J101.53 (GND), J101.59 (GND), J101.60 (GND), J101.65 (GND), J101.66 (GND), J101.71 (GND), J101.74 (GND), J101.98 (GND), J102.107 (GND), J102.108 (GND), J102.113 (GND), J102.114 (GND), J102.119 (GND), J102.120 (GND), J102.125 (GND), J102.126 (GND), J102.131 (GND), J102.132 (GND), J102.137 (GND), J102.138 (GND), J102.144 (GND), J102.150 (GND), J102.155 (GND), J102.156 (GND), J102.161 (GND), J102.162 (GND), J102.167 (GND), J102.168 (GND), J102.173 (GND), J102.174 (GND), J102.179 (GND), J102.180 (GND), J102.185 (GND), J102.186 (GND), J102.191 (GND), J102.192 (GND), J102.197 (GND), J102.198 (GND), J502.3, J503.2, J503.6, J701.1 (GND), J701.3 (GND), J701.9 (GND), J701.15 (GND), J701.21 (GND), J701.27 (GND), J701.33 (GND), J701.39 (GND), J701.45 (GND), J701.51 (GND), J701.57 (GND), J701.71 (GND), J701.73 (GND), J701.75 (GND), J701.S1, J701.S2, R3.2, R20.2, R21.2, R104.1, R704.2, R706.2, SW101.1, SW101.4, SW101.5, SW501.2, SW501.3, SW501.4, SW501.5, TP104.1, TP105.1, TP106.1, U602.3 (GND), U701.2 (GND), U702.4 (PGND), U702.8 (SGND), U702.9 (PAD), U703.2 (GND)
GPIO5: J1.8, J101.34 (GPIO5)
GPIO6: J1.9, J101.30 (GPIO6)
GPIO9: J1.6, J101.40 (GPIO9)
GPIO10: J1.5, J101.44 (GPIO10)
GPIO11: J1.7, J101.38 (GPIO11)
GPIO13: J1.10, J101.28 (GPIO13)
GPIO17: J1.4, J101.50 (GPIO17)
GPIO22: J1.3, J101.46 (GPIO22)
M2_3V3: C707.1, C708.1, C709.1, C710.1, C711.1, C712.1, D702.2 (A), J701.2 (3.3V), J701.4 (3.3V), J701.12 (3.3V), J701.14 (3.3V), J701.16 (3.3V), J701.18 (3.3V), J701.70 (3.3V), J701.72 (3.3V), J701.74 (3.3V), L701.2, R705.1, U703.1 (EN), U703.4 (VDD)
unnamed: D605.1 (K), R605.1
unnamed: D606.1 (K), R606.1
unnamed: D702.1 (K), R707.1
unnamed: J5.A5 (CC1), R21.1
unnamed: J5.B5 (CC2), R20.1
unnamed: J701.10 (DAS/~DSS/~LED1), R707.2
unnamed: J701.68 (SUSCLK), U703.3 (Out)
unnamed: R605.2, U602.4
unnamed: R3.1, U701.5 (ILIM)
VBUS: J5.A4 (VBUS), J5.A9 (VBUS), J5.B4 (VBUS), J5.B9 (VBUS)
VBUS_USB2.0: C702.1, C703.1, U701.6 (OUT)

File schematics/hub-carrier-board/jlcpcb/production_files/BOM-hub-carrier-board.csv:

Comment,Designator,Footprint,LCSC,Quantity
0R,R102,R_0402_1005Metric,C17168,1
100k,R704,R_0402_1005Metric,C25741,1
100n,"C706,C712",C_0402_1005Metric,C1525,2
100nF,C2,C_0805_2012Metric_Pad1.18x1.45mm_HandSolder,C49678,1
100uF,C702,CP_EIA-3528-21_Kemet-B,C122271,1
10k,"R104,R705",R_0402_1005Metric,C25744,2
10u,"C701,C703,C704,C705,C708,C709,C710,C711",C_0805_2012Metric,C15850,8
2.2uH,L701,L_Coilcraft_XAL5030-XXX,C5349681,1
2k2,"R501,R502,R605,R606,R706,R707",R_0402_1005Metric,C25879,6
4.7nF,C707,C_0402_1005Metric,C106208,1
470,C1,CP_Elec_6.3x7.7,C2827940,1
4u7,C601,C_0805_2012Metric,C1779,1
5.1K,"R20,R21",C_0402_1005Metric,C25905,2
AP22653W6,U701,SOT-23-6,C2158037,1
AP3441SHE-7B,U702,DFN-8-1EP_2x2mm_P0.5mm_EP1.05x1.75mm,C2072094,1
ASEK-32.768KHZ-L-R-T,U703,Crystal_SMD_3225-4Pin_3.2x2.5mm,C2650753,1
Bus_M.2_Socket_M,J701,M.2 M Key socket_2230_2242,C841666,1
ComputeModule5-CM5,"J101,J102",Raspberry-Pi-5-Compute-Module_GPIO,C6782225,2
GPIO1,J1,IDC-Header_2x06_P2.54mm_Vertical,C9136,1
GREEN,"D605,D606,D702",LED-SMD_L1.7-W0.6-RD,C2286,3
I2C,J502,JST_SH_BM04B-SRSS-TB_1x04-1MP_P1.00mm_Vertical,C160390,1
MK-11C04-G013,SW101,SW-SMD_MK-11C04-G013,C778185,1
RCLAMP0502BA,"D502,D701",SOT-416,C117553,2
SM02B-SRSS-TB (LF)(SN),CN1,CONN-SMD_2P-P1.00_SM02B-SRSS-TB-LF-SN,C160402,1
SN74LVC1G14DBVR,U602,SOT-353_SC-70-5,C35740,1
SPI,J503,JST_SH_BM10B-SRSS-TB_1x10-1MP_P1.00mm_Vertical,C265443,1
TS-1010A-B,SW501,SW-SMD_TS-1010A-B,C381059,1
USB_C_Receptacle_USB2.0_16P,J5,USB_C_Receptacle_G-Switch_GT-USB-7051x,C2843970,1
M.2 Solder Nut,M702,MountingHole_3mm_Pad,,1
PWR,J2,JST_PH_B2B-PH-K_1x02_P2.00mm_Vertical,,1
15k,R3,R_0402_1005Metric,,1

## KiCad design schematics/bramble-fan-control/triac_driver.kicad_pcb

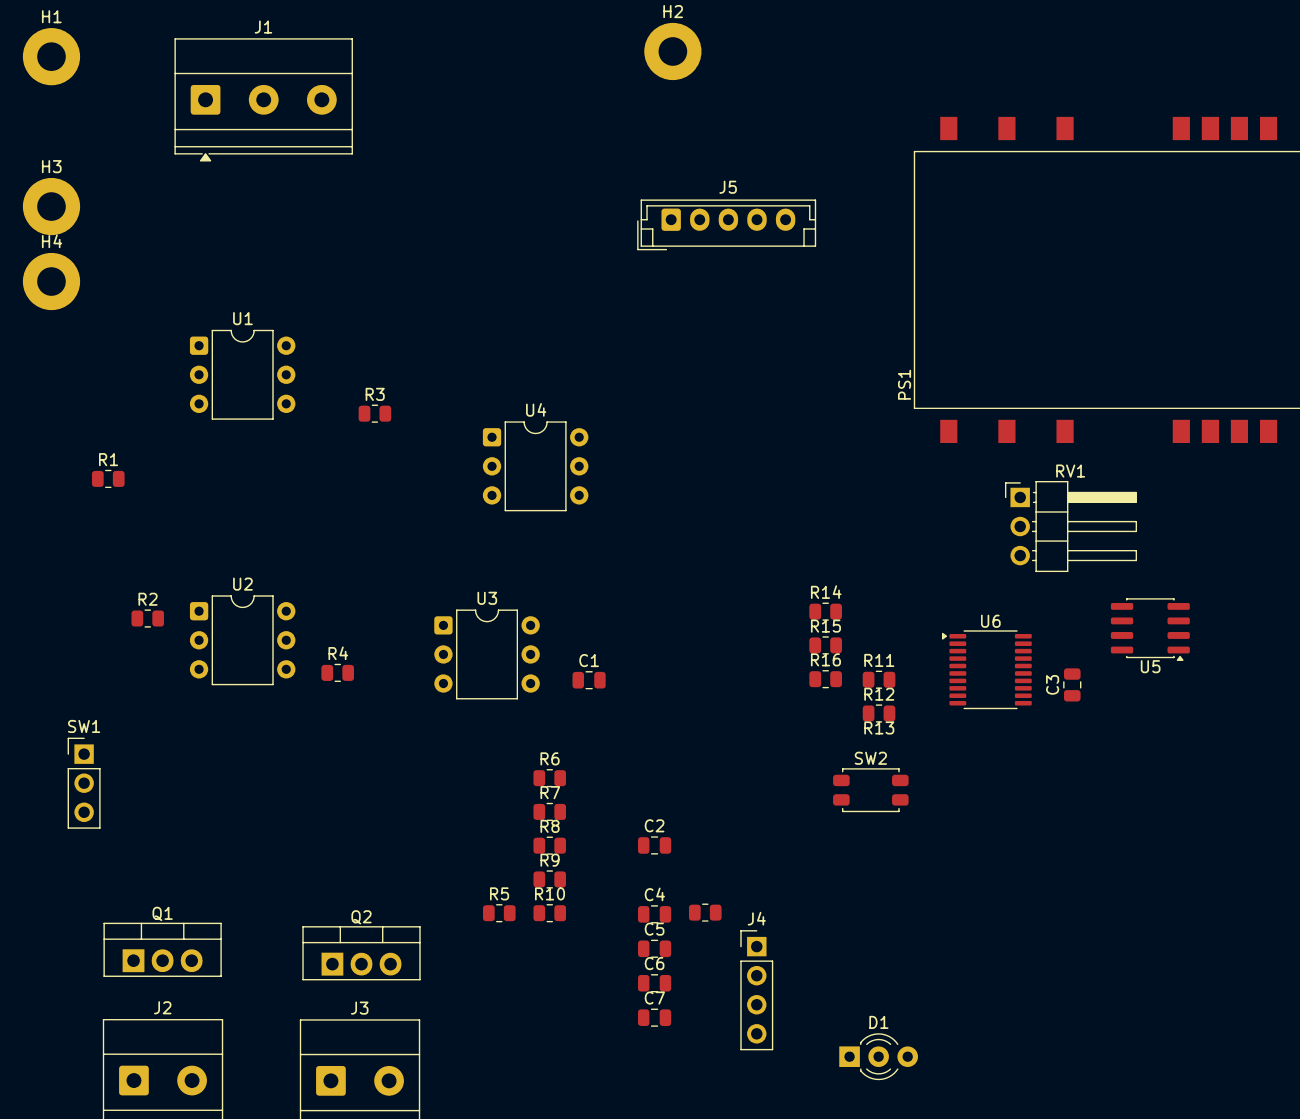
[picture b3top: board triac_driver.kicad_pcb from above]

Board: 2 copper layers, 46 parts (1 on the bottom side), 40 nets, no tracks yet.

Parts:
C1: 10uF; C_0805_2012Metric
C2, C3, C4, C6, C7, C8: 100nF; C_0805_2012Metric
C5: 4.7uF; C_0805_2012Metric
D1: LED_Dual_AKA; LED_D3.0mm-3
H1, H2, H3, H4: MountingHole_Pad; MountingHole_2.5mm_Pad
J1: Conn_01x03_Pin; TerminalBlock_Phoenix_MKDS-1,5-3-5.08_1x03_P5.08mm_Horizont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
J2: FAN_1; TerminalBlock_Phoenix_MKDS-1,5-2-5.08_1x02_P5.08mm_Horizont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
J3: FAN_2; TerminalBlock_Phoenix_MKDS-1,5-2-5.08_1x02_P5.08mm_Horizont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
J4: Conn_01x04_Pin; PinHeader_1x04_P2.54mm_Vertical
J5: Conn_01x05_Pin; JST_EH_B5B-EH-A_1x05_P2.50mm_Vertical
PS1: IRM-02-3.3S; Converter_ACDC_MeanWell_IRM-02-xx_SMD
Q1, Q2: BTA16-600SW3G; TO-220-3_Vertical
R1, R2: 180; R_0805_2012Metric
R3, R4: 330; R_0805_2012Metric
R5, R6, R7, R8, R9, R10, R13, R14, R15, R16: 10k; R_0805_2012Metric
R11, R12: 150; R_0805_2012Metric
RV1: R_Potentiometer_US; PinHeader_1x03_P2.54mm_Horizontal
SW1: SW_Rotary_1x3_MP; PinHeader_1x03_P2.54mm_Vertical
SW2: STM_RESET; SW_SPST_EVQP2_MiddlePushTravel_H2.5mm
U1, U2: MOC3021; DIP-6_W7.62mm
U3, U4: H11AA1; DIP-6_W7.62mm
U5: ADuM1201AR; SOIC-8_3.9x4.9mm_P1.27mm
U6: STM32L031F6P6TR; TSSOP-20_4.4x6.5mm_P0.65mm

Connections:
+3.3V: U3.4 (C), U4.4 (C)
/AUTO: R16.1, SW1.3, U6.3 (PC15-OSC32_OUT)
/OFF: R15.1, SW1.1, U6.2 (PC14-OSC32_IN)
/ON: R13.1, SW1.2, U6.13 (PA7)
/mcu/FAN_SETTING: C3.1, RV1.2, U6.12 (PA6)
/mcu/NRST: C8.2, J5.4, SW2.1, U6.4 (NRST)
/mcu/TRIAC_1_CTRL: R1.1, U6.6 (PA0-CK_IN)
/mcu/TRIAC_2_CTRL: R2.1, U6.7 (PA1)
/mcu/UART_RX: U5.6 (VOB), U6.18 (PA10)
/mcu/UART_TX: U5.7 (VIA), U6.17 (PA9)
/mcu/ZC_1_DETECT: R9.1, U3.5 (E), U6.8 (PA2)
/mcu/ZC_2_DETECT: R10.1, U4.5 (E), U6.9 (PA3)
GND: C1.2, C3.2, C4.2, C5.2, C6.2, C7.2, C8.1, D1.2 (K), J1.3, J5.5, PS1.13 (-Vo), R9.2, R10.2, R13.2, R14.2, R15.2, R16.2, RV1.3, SW2.2, U1.2 (K), U2.2 (K), U5.5 (GND2), U6.15 (VSS)
LINE: J1.1, J2.1, J3.1, PS1.1 (AC/L), R5.1, R7.1
NEUT: J1.2, PS1.24 (AC/N)
NEUTRAL: Q1.2 (MT1), Q2.2 (MT1), R6.1, R8.1, U1.6 (MT1), U2.6 (MT1)
unnamed: D1.1 (A1), R11.1
unnamed: D1.3 (A2), R12.1
unnamed: J2.2, Q1.1 (MT2)
unnamed: J3.2, Q2.1 (MT2)
unnamed: C2.1, J4.1, U5.1 (VDD1)
unnamed: J4.2, U5.2 (VOA)
unnamed: J4.3, U5.3 (VIB)
unnamed: C2.2, J4.4, U5.4 (GND1)
unnamed: J5.2, U6.20 (PA14)
unnamed: J5.3, U6.19 (PA13)
unnamed: Q1.3 (G), R3.2
unnamed: Q2.3 (G), R4.2
unnamed: R1.2, U1.1 (A)
unnamed: R3.1, U1.4 (MT2)
unnamed: R2.2, U2.1 (A)
unnamed: R4.1, U2.4 (MT2)
unnamed: R5.2, U3.1 (AC1)
unnamed: R6.2, U3.2 (AC2)
unnamed: R7.2, U4.1 (AC1)
unnamed: R8.2, U4.2 (AC2)
unnamed: R11.2, U6.10 (PA4)
unnamed: R12.2, U6.11 (PA5)
unnamed: R14.1, U6.1 (PB9-BOOT0)
VDD: C1.1, C4.1, C5.1, C6.1, C7.1, J5.1, PS1.12 (+Vo), RV1.1, U5.8 (VDD2), U6.5 (VDDA), U6.16 (VDD)
